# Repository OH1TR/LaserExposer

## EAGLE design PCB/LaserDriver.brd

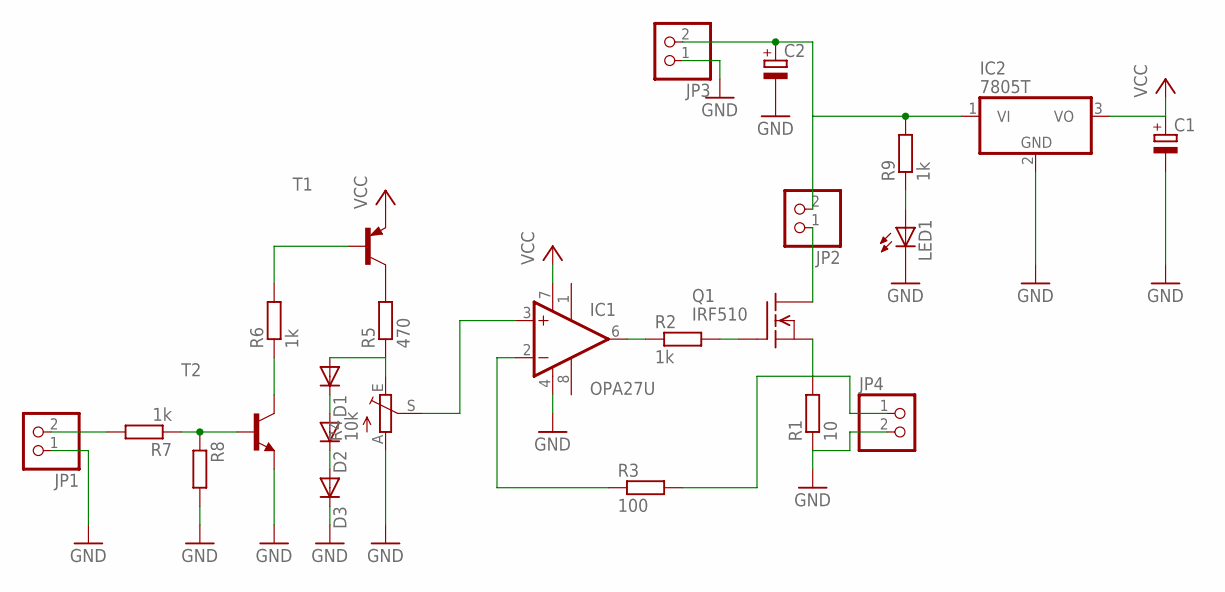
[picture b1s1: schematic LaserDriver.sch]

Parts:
C1, C2: CPOL-EUE5-10.5; E5-10,5
D1, D2, D3: DIODE-DO214AA; DO214AA
IC1: OPA27U; SO08
IC2: 7805T; TO220H
JP1, JP2, JP3, JP4: PINHD-1X2; 1X02
LED1: LEDCHIP-LED0805; CHIP-LED0805
Q1: IRF510; TO220
R1: 10; 0207/10
R2, R6, R7, R9: 1k; R1206
R3: 100; R1206
R4: 10k; SP19L
R5: 470; R1206
R8: R-EU_R1206; R1206
T1: MMBT3906LT1-PNP-SOT23-BEC; SOT23-BEC
T2: BC817-16-NPN-SOT23-BEC; SOT23-BEC

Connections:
GND: C1.-, C2.-, D3.C, IC1.4 (V-), IC2.2 (GND), JP1.1, JP3.1, JP4.2, LED1.C, R1.1, R4.A, R8.2, T2.E
unnamed: JP4.1, Q1.3 (S), R1.2, R3.2
unnamed: Q1.1 (G), R2.2
unnamed: IC1.2 (-IN), R3.1
unnamed: IC1.6 (OUT), R2.1
unnamed: IC1.3 (+IN), R4.S
unnamed: D1.A, R4.E, R5.1
unnamed: R5.2, T1.C
unnamed: R6.2, T1.B
unnamed: R6.1, T2.C
unnamed: R7.1, R8.1, T2.B
unnamed: JP1.2, R7.2
unnamed: D1.C, D2.A
unnamed: D2.C, D3.A
unnamed: JP2.1, Q1.2 (D)
unnamed: C2.+, IC2.1 (VI), JP2.2, JP3.2, R9.2
unnamed: LED1.A, R9.1
VCC: C1.+, IC1.7 (V+), IC2.3 (VO), T1.E

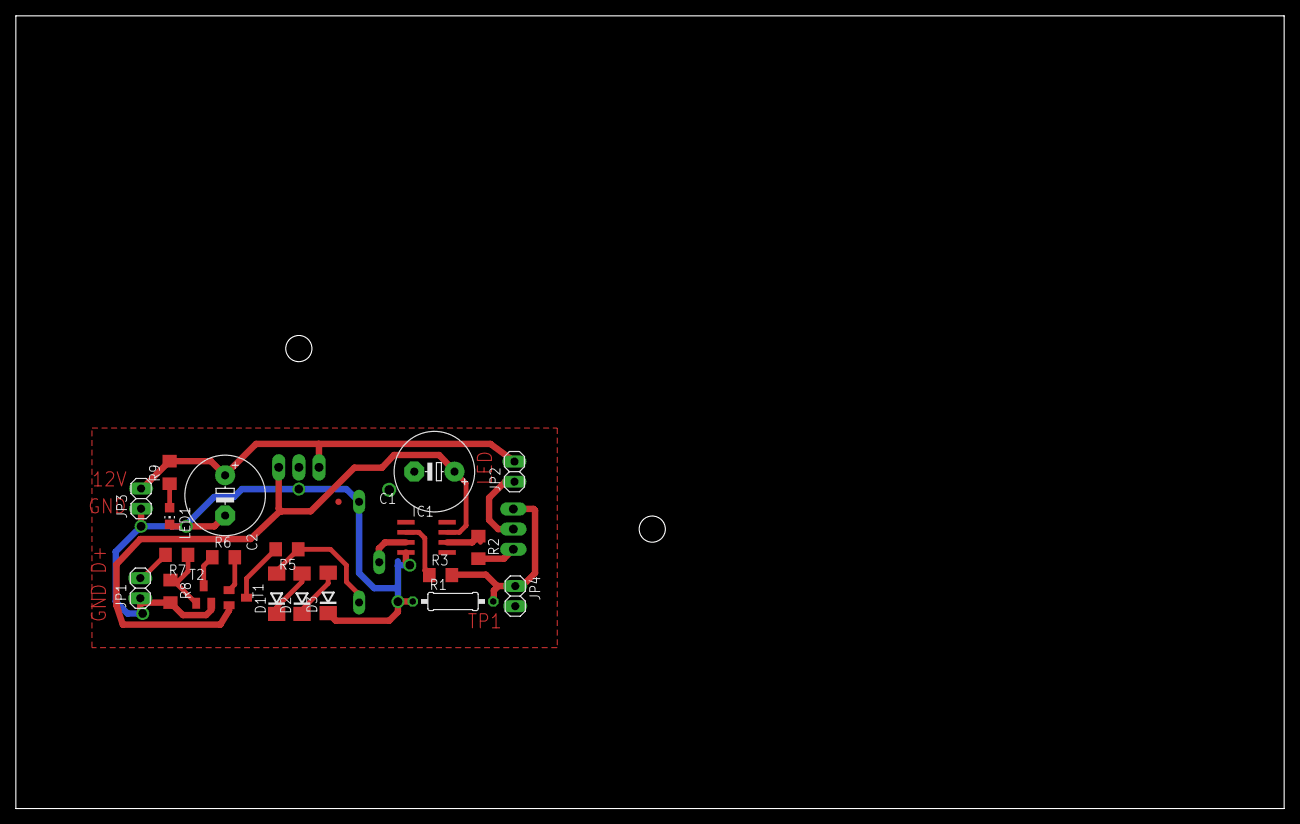
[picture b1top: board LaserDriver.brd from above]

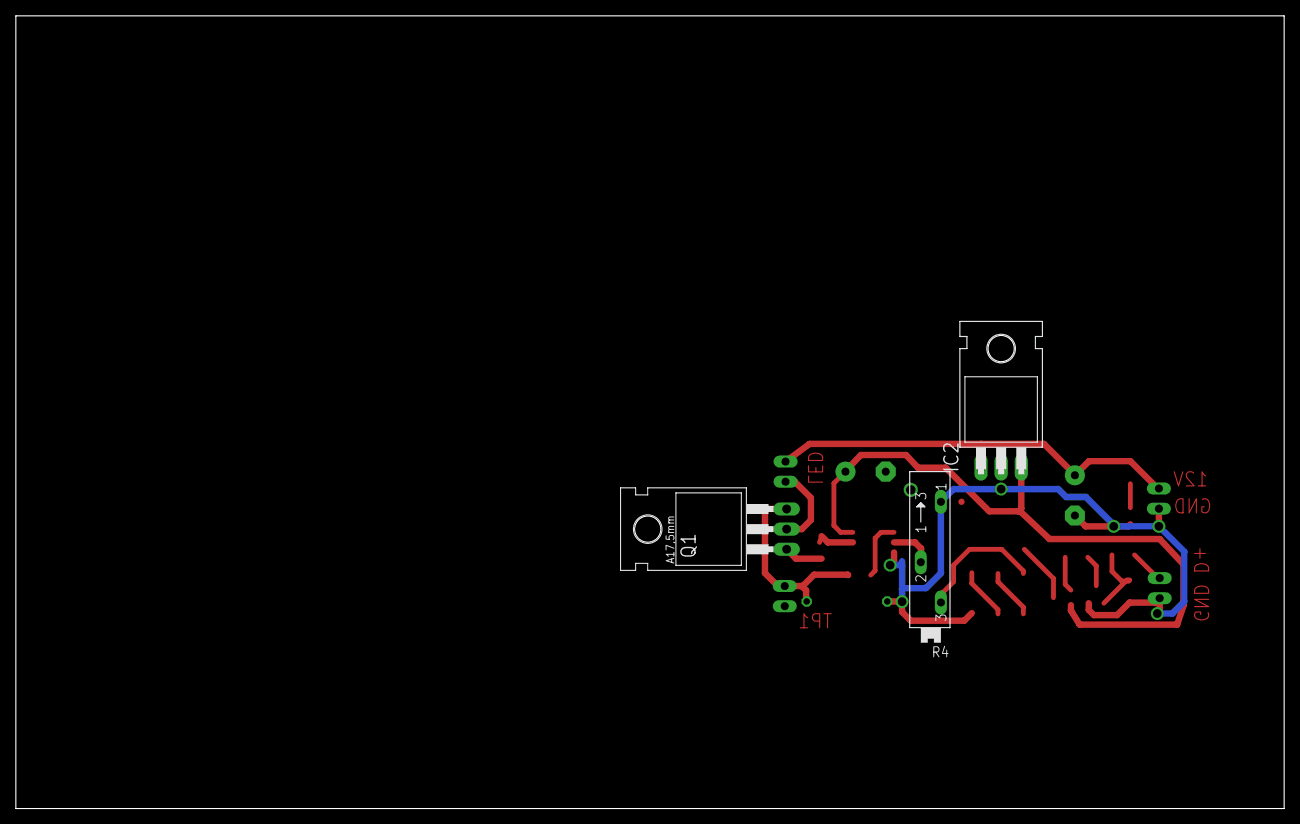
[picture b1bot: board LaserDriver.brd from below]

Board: 2 copper layers, 160.0 x 100.0 mm, 24 parts (3 on the bottom side), 18 nets.

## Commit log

2018-01-01 Fixed python code
2018-01-01 Folder rename
2018-01-01 Install script
2018-01-02 Fixed component placement issues and modified directory tree.
2018-01-04 Added possibility set print sweep time. Fixed laser driver layout.
2019-02-18 Added move to end stop.
